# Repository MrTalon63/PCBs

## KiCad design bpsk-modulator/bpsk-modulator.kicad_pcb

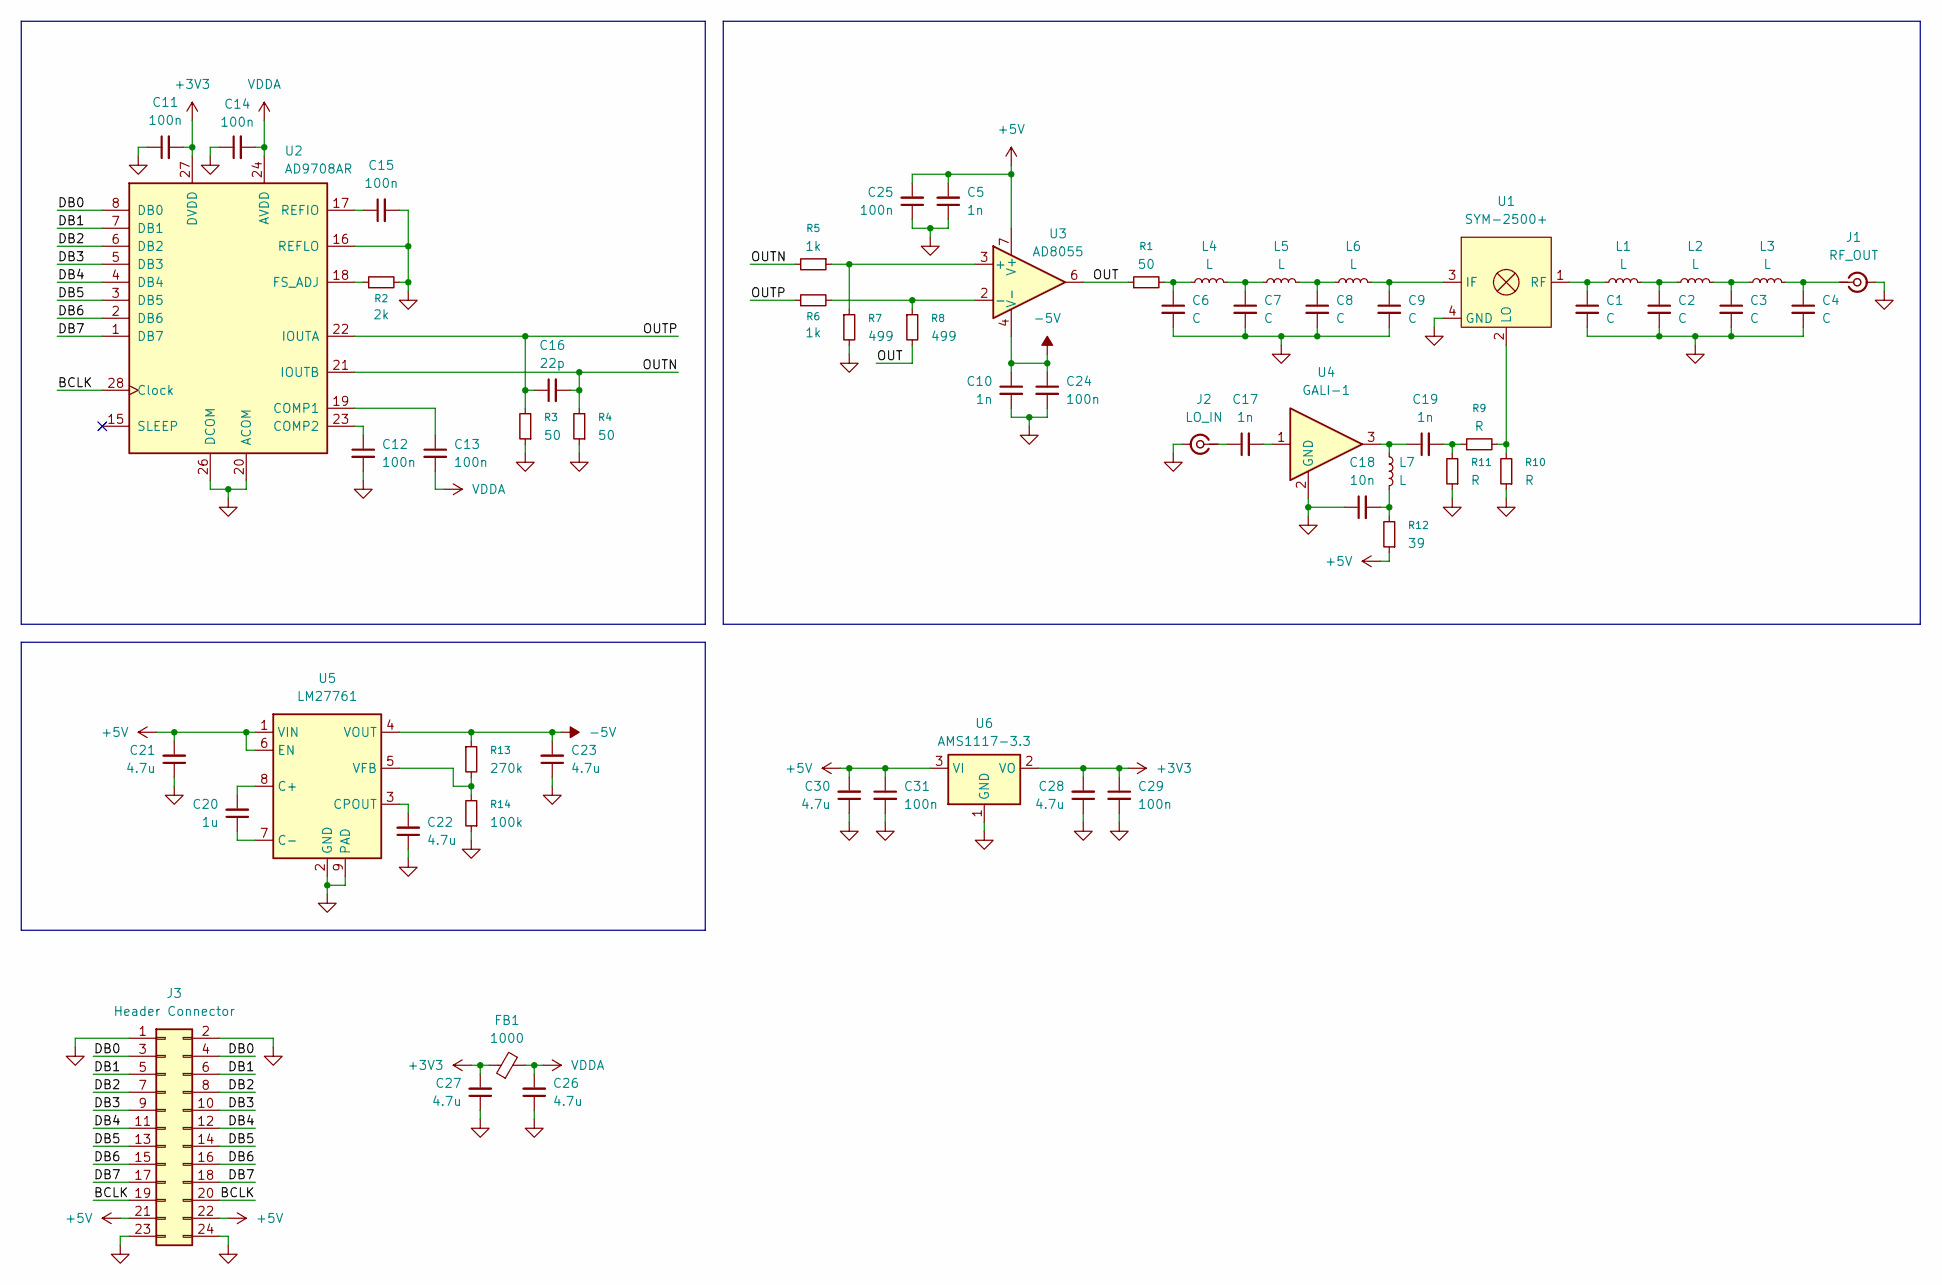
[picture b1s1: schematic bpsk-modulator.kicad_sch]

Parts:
C1, C2, C3, C4: C; C_0402_1005Metric
C5, C10, C17, C19: 1n; C_0603_1608Metric_Pad1.08x0.95mm_HandSolder
C6, C7, C8, C9: C; C_0603_1608Metric_Pad1.08x0.95mm_HandSolder
C11, C12, C13, C14, C15, C24, C25, C29, C31: 100n; C_0603_1608Metric_Pad1.08x0.95mm_HandSolder
C16: 22p; C_0603_1608Metric_Pad1.08x0.95mm_HandSolder
C18: 10n; C_0603_1608Metric_Pad1.08x0.95mm_HandSolder
C20: 1u; C_0603_1608Metric_Pad1.08x0.95mm_HandSolder
C21, C22, C23, C26, C27, C28, C30: 4.7u; C_0603_1608Metric_Pad1.08x0.95mm_HandSolder
FB1: 1000; L_0603_1608Metric
J1: RF_OUT; SMA_Samtec_SMA-J-P-H-ST-EM1_EdgeMount
J2: LO_IN; SMA_Samtec_SMA-J-P-H-ST-EM1_EdgeMount
J3: Header Connector; PinHeader_2x12_P2.54mm_Vertical
L1, L2, L3: L; L_0402_1005Metric
L4, L5, L6, L7: L; L_0603_1608Metric
R1, R3, R4: 50; R_0603_1608Metric_Pad0.98x0.95mm_HandSolder
R2: 2k; R_0603_1608Metric_Pad0.98x0.95mm_HandSolder
R5, R6: 1k; R_0603_1608Metric_Pad0.98x0.95mm_HandSolder
R7, R8: 499; R_0603_1608Metric_Pad0.98x0.95mm_HandSolder
R9, R10, R11: R; R_0603_1608Metric_Pad0.98x0.95mm_HandSolder
R12: 39; R_0603_1608Metric_Pad0.98x0.95mm_HandSolder
R13: 270k; R_0603_1608Metric_Pad0.98x0.95mm_HandSolder
R14: 100k; R_0603_1608Metric_Pad0.98x0.95mm_HandSolder
U1: SYM-2500+; Mini-Circuits_TTT167_LandPatternPL-079
U2: AD9708AR; TSSOP-28_4.4x9.7mm_P0.65mm
U3: AD8055; SOIC-8_3.9x4.9mm_P1.27mm
U4: GALI-1; SOT-89-3
U5: LM27761; WSON-8-1EP_2x2mm_P0.5mm_EP0.9x1.6mm
U6: AMS1117-3.3; SOT-223-3_TabPin2

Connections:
+3V3: C11.2, C27.2, C28.2, C29.1, FB1.1, U2.27 (DVDD), U6.2 (VO)
+5V: C5.2, C21.2, C25.2, C30.2, C31.1, J3.21, J3.22, R12.1, U3.7 (V+), U5.1 (VIN), U5.6 (EN), U6.3 (VI)
-5V: C10.1, C23.2, C24.1, R13.1, U3.4 (V-), U5.4 (VOUT)
/BCLK: J3.19, J3.20, U2.28 (Clock)
/DB0: J3.3, J3.4, U2.8 (DB0)
/DB1: J3.5, J3.6, U2.7 (DB1)
/DB2: J3.7, J3.8, U2.6 (DB2)
/DB3: J3.9, J3.10, U2.5 (DB3)
/DB4: J3.11, J3.12, U2.4 (DB4)
/DB5: J3.13, J3.14, U2.3 (DB5)
/DB6: J3.15, J3.16, U2.2 (DB6)
/DB7: J3.17, J3.18, U2.1 (DB7)
/OUT: R1.1, R8.2, U3.6
/OUTN: C16.2, R4.2, R5.2, U2.21 (IOUTB)
/OUTP: C16.1, R3.2, R6.1, U2.22 (IOUTA)
GND: C1.2, C2.2, C3.2, C4.2, C5.1, C6.2, C7.2, C8.2, C9.2, C10.2, C11.1, C12.2, C14.1, C15.2, C18.1, C21.1, C22.1, C23.1, C24.2, C25.1, C26.1, C27.1, C28.1, C29.2, C30.1, C31.2, J1.2 (Ext), J2.2 (Ext), J3.1, J3.2, J3.23, J3.24, R2.2, R3.1, R4.1, R7.2, R10.1, R11.1, R14.1, U1.4 (GND), U2.16 (REFLO), U2.20 (ACOM), U2.26 (DCOM), U4.2 (GND), U5.2 (GND), U5.9 (PAD), U6.1 (GND)
unnamed: C2.1, L1.2, L2.1
unnamed: C3.1, L2.2, L3.1
unnamed: C6.1, L4.1, R1.2
unnamed: C7.1, L4.2, L5.1
unnamed: C8.1, L5.2, L6.1
unnamed: C17.2, U4.1
unnamed: C18.2, L7.2, R12.2
unnamed: C19.1, L7.1, U4.3
unnamed: C19.2, R9.1, R11.2
unnamed: C4.1, J1.1 (In), L3.2
unnamed: C17.1, J2.1 (In)
unnamed: C9.1, L6.2, U1.3 (IF)
unnamed: R9.2, R10.2, U1.2 (LO)
unnamed: C1.1, L1.1, U1.1 (RF)
unnamed: C13.1, U2.19 (COMP1)
unnamed: C12.1, U2.23 (COMP2)
unnamed: R2.1, U2.18 (FS_ADJ)
unnamed: C15.1, U2.17 (REFIO)
unnamed: R5.1, R7.1, U3.3 (+)
unnamed: R6.2, R8.1, U3.2 (-)
unnamed: C20.2, U5.8 (C+)
unnamed: C20.1, U5.7 (C-)
unnamed: C22.2, U5.3 (CPOUT)
unnamed: R13.2, R14.2, U5.5 (VFB)
VDDA: C13.2, C14.2, C26.2, FB1.2, U2.24 (AVDD)

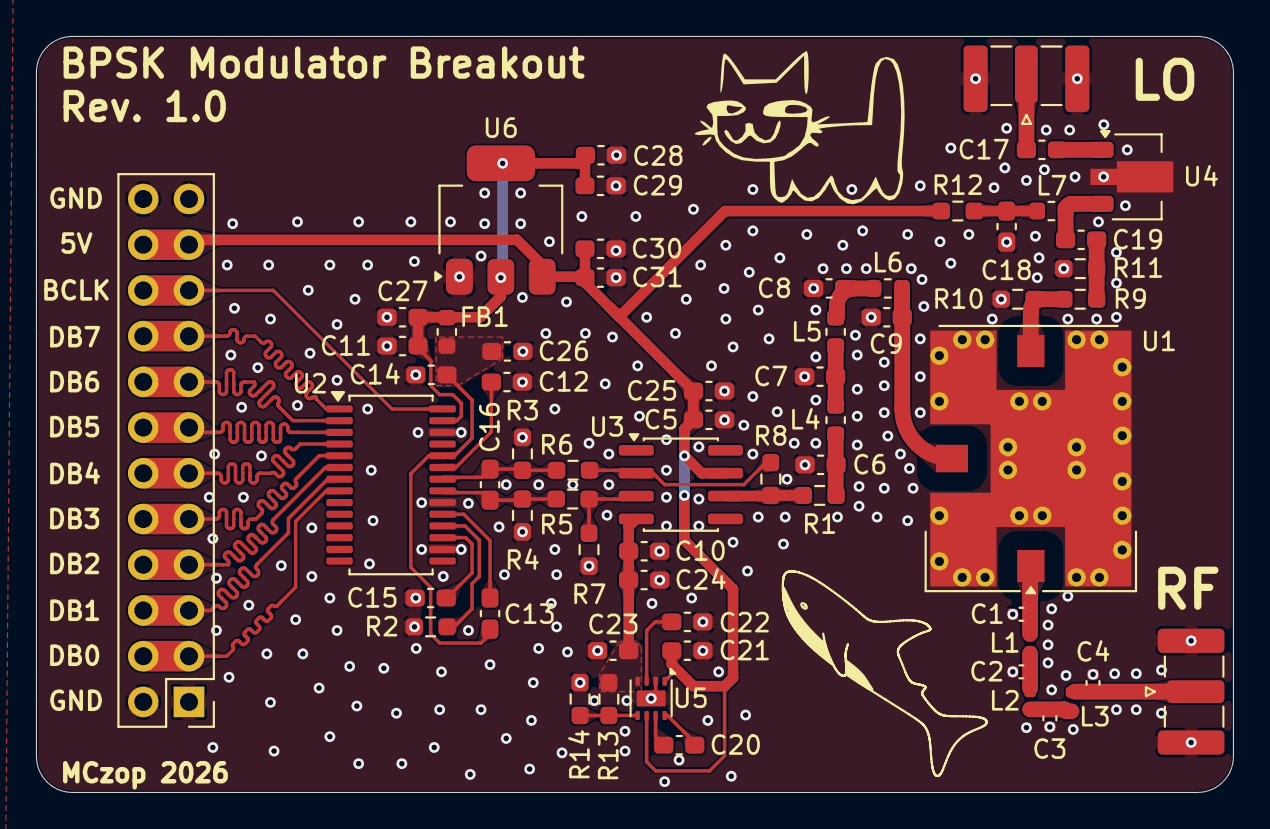
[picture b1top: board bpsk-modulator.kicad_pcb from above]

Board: 2 copper layers, 66.5 x 42.0 mm, 62 parts (0 on the bottom side), 41 nets.

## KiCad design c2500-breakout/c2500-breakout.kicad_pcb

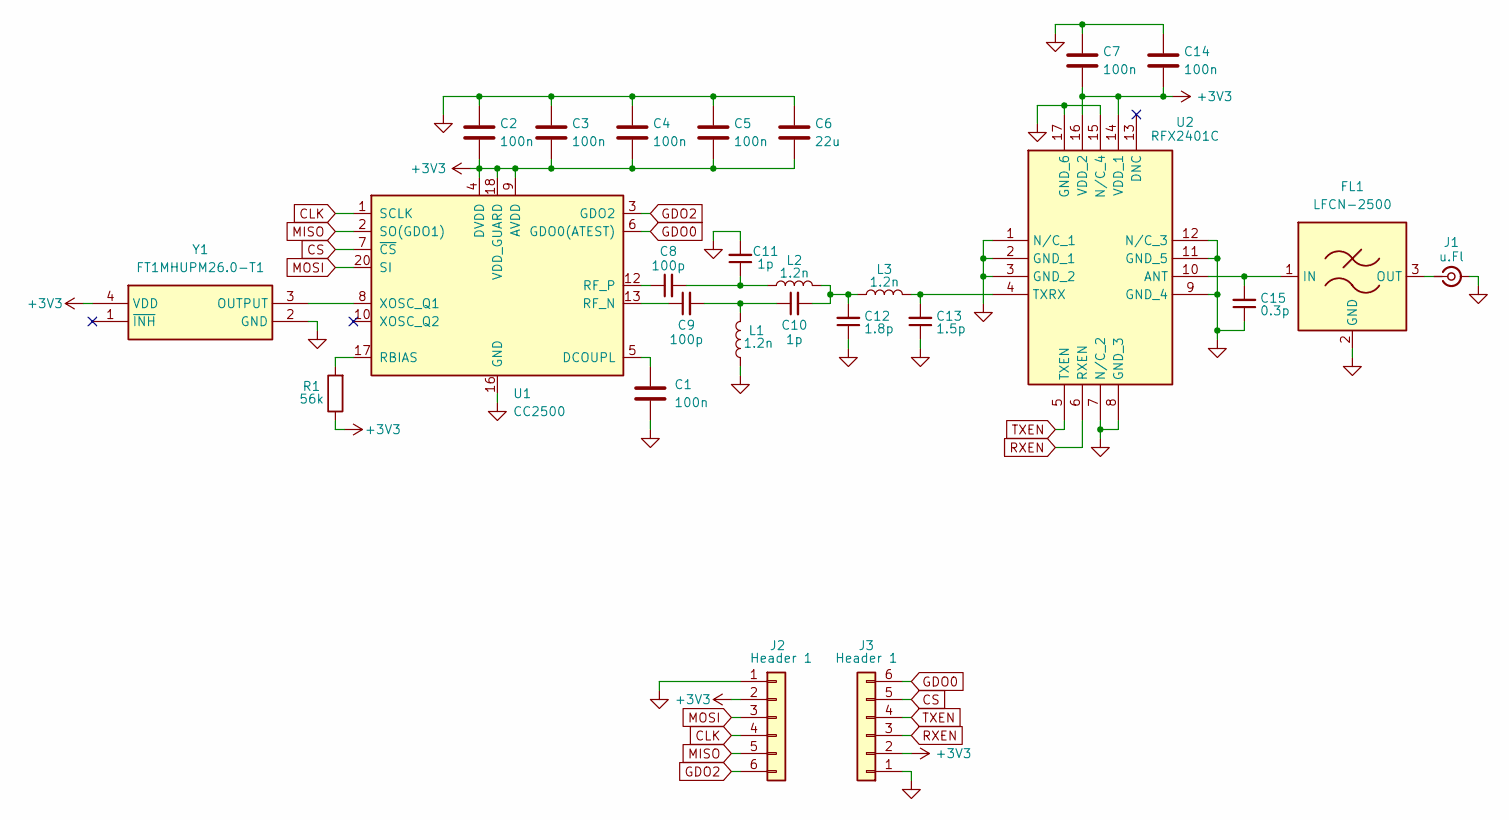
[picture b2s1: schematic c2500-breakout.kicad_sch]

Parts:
C1, C2, C3, C4, C5, C7, C14: 100n; C_0603_1608Metric_Pad1.08x0.95mm_HandSolder
C6: 22u; C_0603_1608Metric_Pad1.08x0.95mm_HandSolder
C8, C9: 100p; C_0402_1005Metric_Pad0.74x0.62mm_HandSolder
C10, C11: 1p; C_0402_1005Metric_Pad0.74x0.62mm_HandSolder
C12: 1.8p; C_0402_1005Metric_Pad0.74x0.62mm_HandSolder
C13: 1.5p; C_0402_1005Metric_Pad0.74x0.62mm_HandSolder
C15: 0.3p; C_0402_1005Metric_Pad0.74x0.62mm_HandSolder
FL1: LFCN-2500; Filter_Mini-Circuits_FV1206
J1: u.Fl; U.FL_Molex_MCRF_73412-0110_Vertical
J2, J3: Header 1; PinHeader_1x06_P2.54mm_Vertical
L1, L2, L3: 1.2n; L_0402_1005Metric_Pad0.77x0.64mm_HandSolder
R1: 56k; R_0603_1608Metric_Pad0.98x0.95mm_HandSolder
U1: CC2500; Texas_RGP0020H_VQFN-20-1EP_4x4mm_P0.5mm_EP2.4x2.4mm
U2: RFX2401C; QFN50P300X300X60-17N-D; Mouser Part Number 477-RFX2401C
Y1: FT1MHUPM26.0-T1; FT1MHUPM260T1; Manufacturer_Part_Number FT1MHUPM26.0-T1

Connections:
+3V3: C2.2, C3.2, C4.2, C5.2, C6.2, C7.2, C14.2, J2.2, J3.2, R1.1, U1.4 (DVDD), U1.9 (AVDD), U1.11 (AVDD), U1.14 (AVDD), U1.15 (AVDD), U1.18 (VDD_GUARD), U2.14 (VDD_1), U2.16 (VDD_2), Y1.4 (VDD)
CLK: J2.4, U1.1 (SCLK)
CS: J3.5, U1.7 (~CS)
GDO0: J3.6, U1.6 (GDO0(ATEST))
GDO2: J2.6, U1.3 (GDO2)
GND: C1.2, C2.1, C3.1, C4.1, C5.1, C6.1, C7.1, C11.2, C12.1, C13.1, C14.1, C15.1, FL1.2 (GND), FL1.4 (GND), J1.2 (Ext), J2.1, J3.1, L1.1, U1.16 (GND), U1.19 (GND), U1.21 (GND), U2.1 (N/C_1), U2.2 (GND_1), U2.3 (GND_2), U2.7 (N/C_2), U2.8 (GND_3), U2.9 (GND_4), U2.11 (GND_5), U2.12 (N/C_3), U2.15 (N/C_4), U2.17 (GND_6), Y1.2 (GND)
MISO: J2.5, U1.2 (SO(GDO1))
MOSI: J2.3, U1.20 (SI)
unnamed: C9.2, C10.1, L1.2
unnamed: C10.2, C12.2, L2.2, L3.1
unnamed: C8.2, C11.1, L2.1
unnamed: C15.2, FL1.1 (IN), U2.10 (ANT)
unnamed: FL1.3 (OUT), J1.1 (In)
unnamed: C1.1, U1.5 (DCOUPL)
unnamed: R1.2, U1.17 (RBIAS)
unnamed: C9.1, U1.13 (RF_N)
unnamed: C8.1, U1.12 (RF_P)
unnamed: U1.8 (XOSC_Q1), Y1.3 (OUTPUT)
unnamed: C13.2, L3.2, U2.4 (TXRX)
RXEN: J3.3, U2.6 (RXEN)
TXEN: J3.4, U2.5 (TXEN)

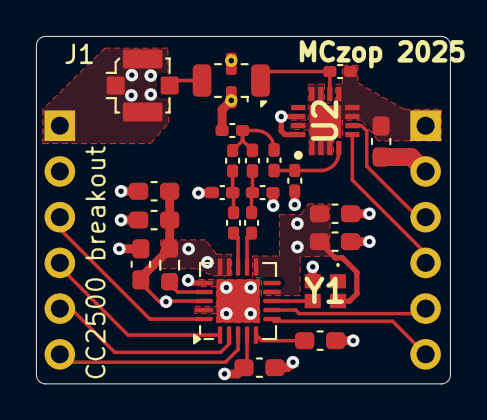
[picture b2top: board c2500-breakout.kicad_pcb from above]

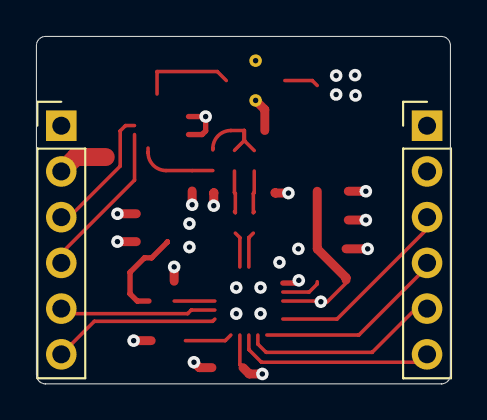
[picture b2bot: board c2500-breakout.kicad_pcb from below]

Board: 6 copper layers, 23.0 x 19.3 mm, 26 parts (2 on the bottom side), 21 nets.

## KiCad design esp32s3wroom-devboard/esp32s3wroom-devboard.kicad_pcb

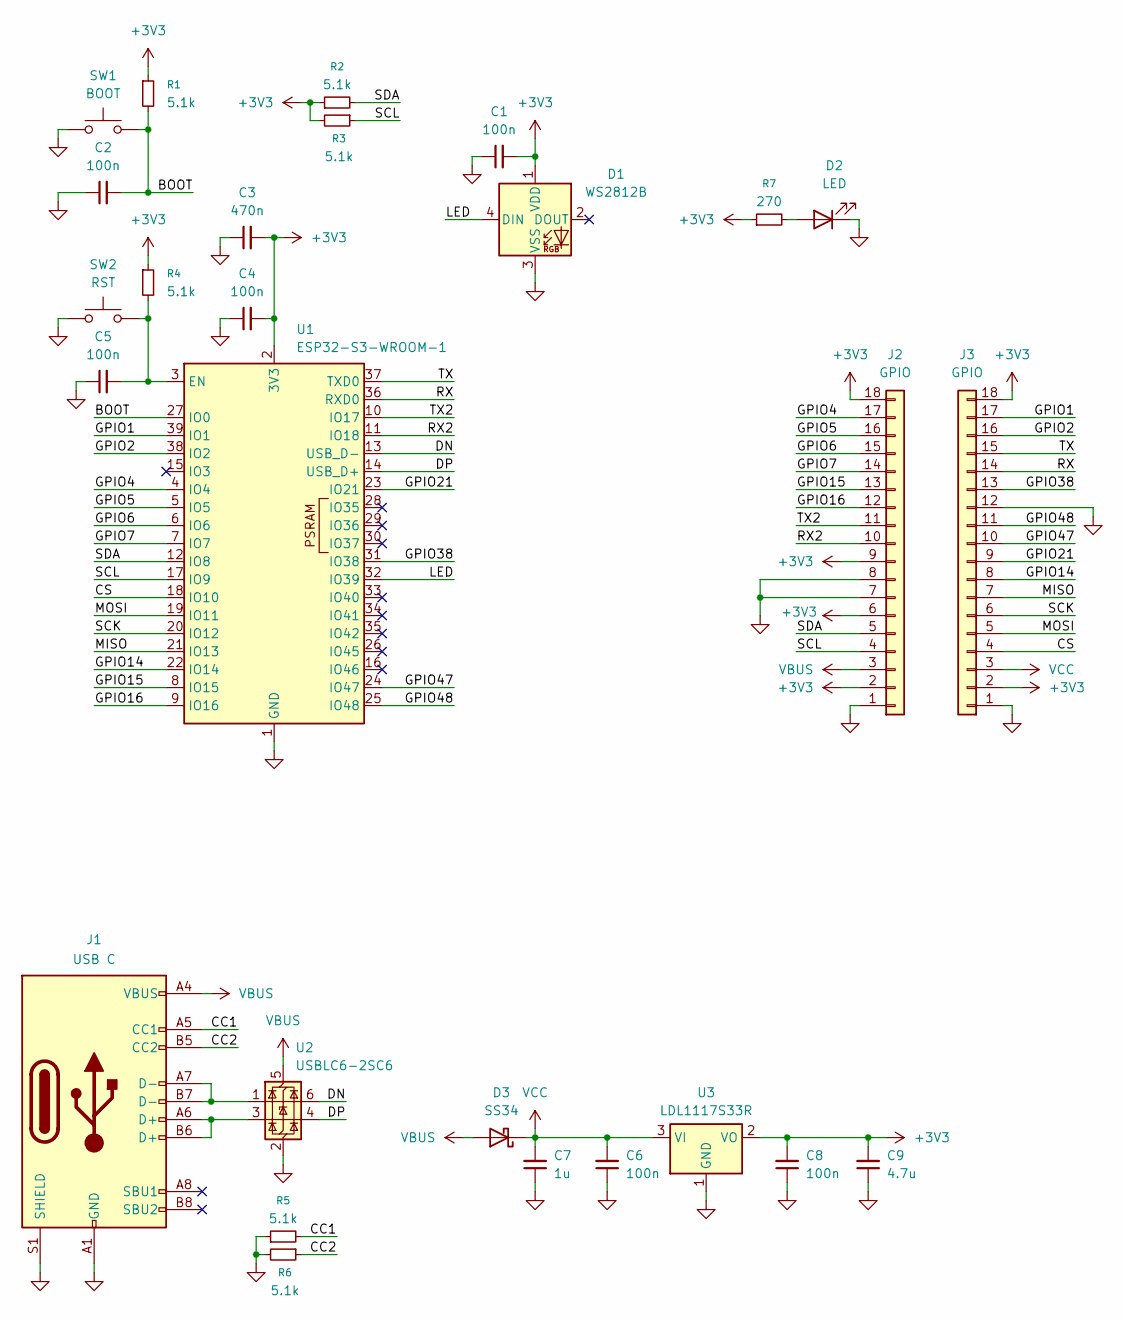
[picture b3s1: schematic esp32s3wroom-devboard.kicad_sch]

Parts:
C1, C2, C4, C5, C6, C8: 100n; C_0402_1005Metric
C3: 470n; C_0402_1005Metric
C7: 1u; C_0603_1608Metric
C9: 4.7u; C_0603_1608Metric
D1: WS2812B; LED_WS2812B_PLCC4_5.0x5.0mm_P3.2mm
D2: LED; LED_0805_2012Metric
D3: SS34; D_SMA
J1: USB C; USB_C_Receptacle_GCT_USB4105-xx-A_16P_TopMnt_Horizontal
J2, J3: GPIO; PinHeader_1x18_P2.54mm_Vertical
R1, R2, R3, R4, R5, R6: 5.1k; R_0402_1005Metric
R7: 270; R_0603_1608Metric
SW1: BOOT; KLS7TS6611
SW2: RST; KLS7TS6611
U1: ESP32-S3-WROOM-1
U2: USBLC6-2SC6; SOT-23-6
U3: LDL1117S33R; SOT-223-3_TabPin2

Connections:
+3V3: C1.2, C3.2, C4.2, C8.2, C9.2, D1.1 (VDD), J2.2, J2.6, J2.9, J2.18, J3.2, J3.18, R1.1, R2.1, R3.2, R4.1, R7.1, U1.2 (3V3), U3.2 (VO)
/BOOT: C2.2, R1.2, SW1.2, U1.27 (IO0)
/CC1: J1.A5 (CC1), R5.2
/CC2: J1.B5 (CC2), R6.1
/CS: J3.4, U1.18 (IO10)
/DN: U1.13 (USB_D-), U2.6 (I/O1)
/DP: U1.14 (USB_D+), U2.4 (I/O2)
/GPIO1: J3.17, U1.39 (IO1)
/GPIO2: J3.16, U1.38 (IO2)
/GPIO4: J2.17, U1.4 (IO4)
/GPIO5: J2.16, U1.5 (IO5)
/GPIO6: J2.15, U1.6 (IO6)
/GPIO7: J2.14, U1.7 (IO7)
/GPIO14: J3.8, U1.22 (IO14)
/GPIO15: J2.13, U1.8 (IO15)
/GPIO16: J2.12, U1.9 (IO16)
/GPIO21: J3.9, U1.23 (IO21)
/GPIO38: J3.13, U1.31 (IO38)
/GPIO47: J3.10, U1.24 (IO47)
/GPIO48: J3.11, U1.25 (IO48)
/LED: D1.4 (DIN), U1.32 (IO39)
/MISO: J3.7, U1.21 (IO13)
/MOSI: J3.5, U1.19 (IO11)
/RX: J3.14, U1.36 (RXD0)
/RX2: J2.10, U1.11 (IO18)
/SCK: J3.6, U1.20 (IO12)
/SCL: J2.4, R3.1, U1.17 (IO9)
/SDA: J2.5, R2.2, U1.12 (IO8)
/TX: J3.15, U1.37 (TXD0)
/TX2: J2.11, U1.10 (IO17)
GND: C1.1, C2.1, C3.1, C4.1, C5.1, C6.1, C7.1, C8.1, C9.1, D1.3 (VSS), D2.1 (K), J1.A1 (GND), J1.A12 (GND), J1.B1 (GND), J1.B12 (GND), J1.S1 (SHIELD), J2.1, J2.7, J2.8, J3.1, J3.12, R5.1, R6.2, SW1.1, SW2.1, U1.1 (GND), U1.40 (GND), U1.41 (GND), U2.2 (GND), U3.1 (GND)
unnamed: D2.2 (A), R7.2
unnamed: J1.A6 (D+), J1.B6 (D+), U2.3 (I/O2)
unnamed: J1.A7 (D-), J1.B7 (D-), U2.1 (I/O1)
unnamed: C5.2, R4.2, SW2.2, U1.3 (EN)
VBUS: D3.2 (A), J1.A4 (VBUS), J1.A9 (VBUS), J1.B4 (VBUS), J1.B9 (VBUS), J2.3, U2.5 (VBUS)
VCC: C6.2, C7.2, D3.1 (K), J3.3, U3.3 (VI)

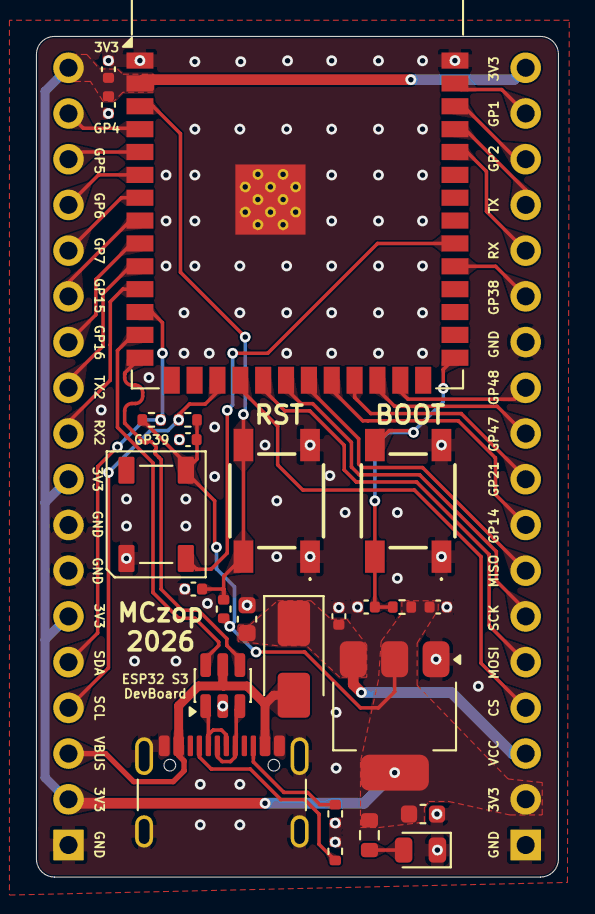
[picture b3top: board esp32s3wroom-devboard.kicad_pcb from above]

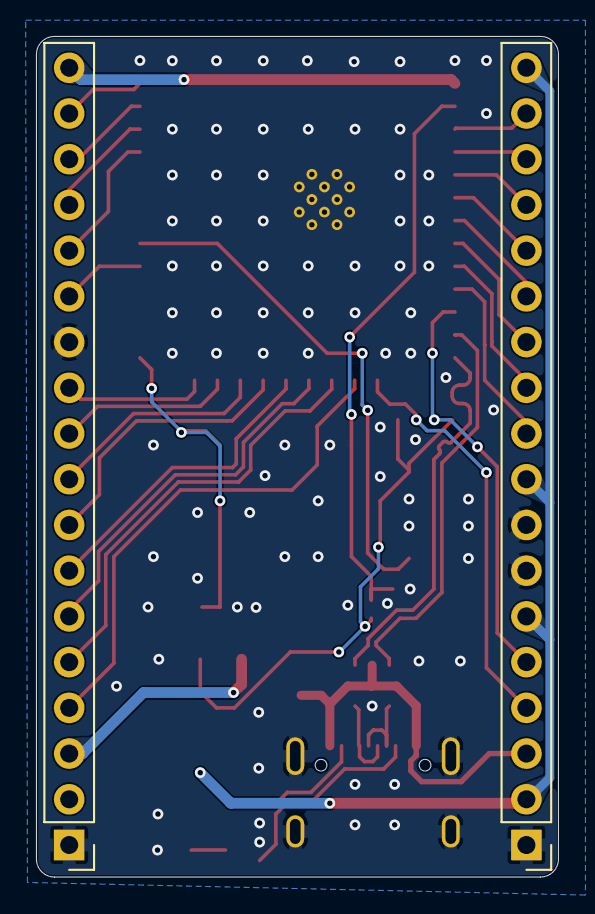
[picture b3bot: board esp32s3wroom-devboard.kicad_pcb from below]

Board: 2 copper layers, 29.0 x 46.7 mm, 27 parts (2 on the bottom side), 37 nets.

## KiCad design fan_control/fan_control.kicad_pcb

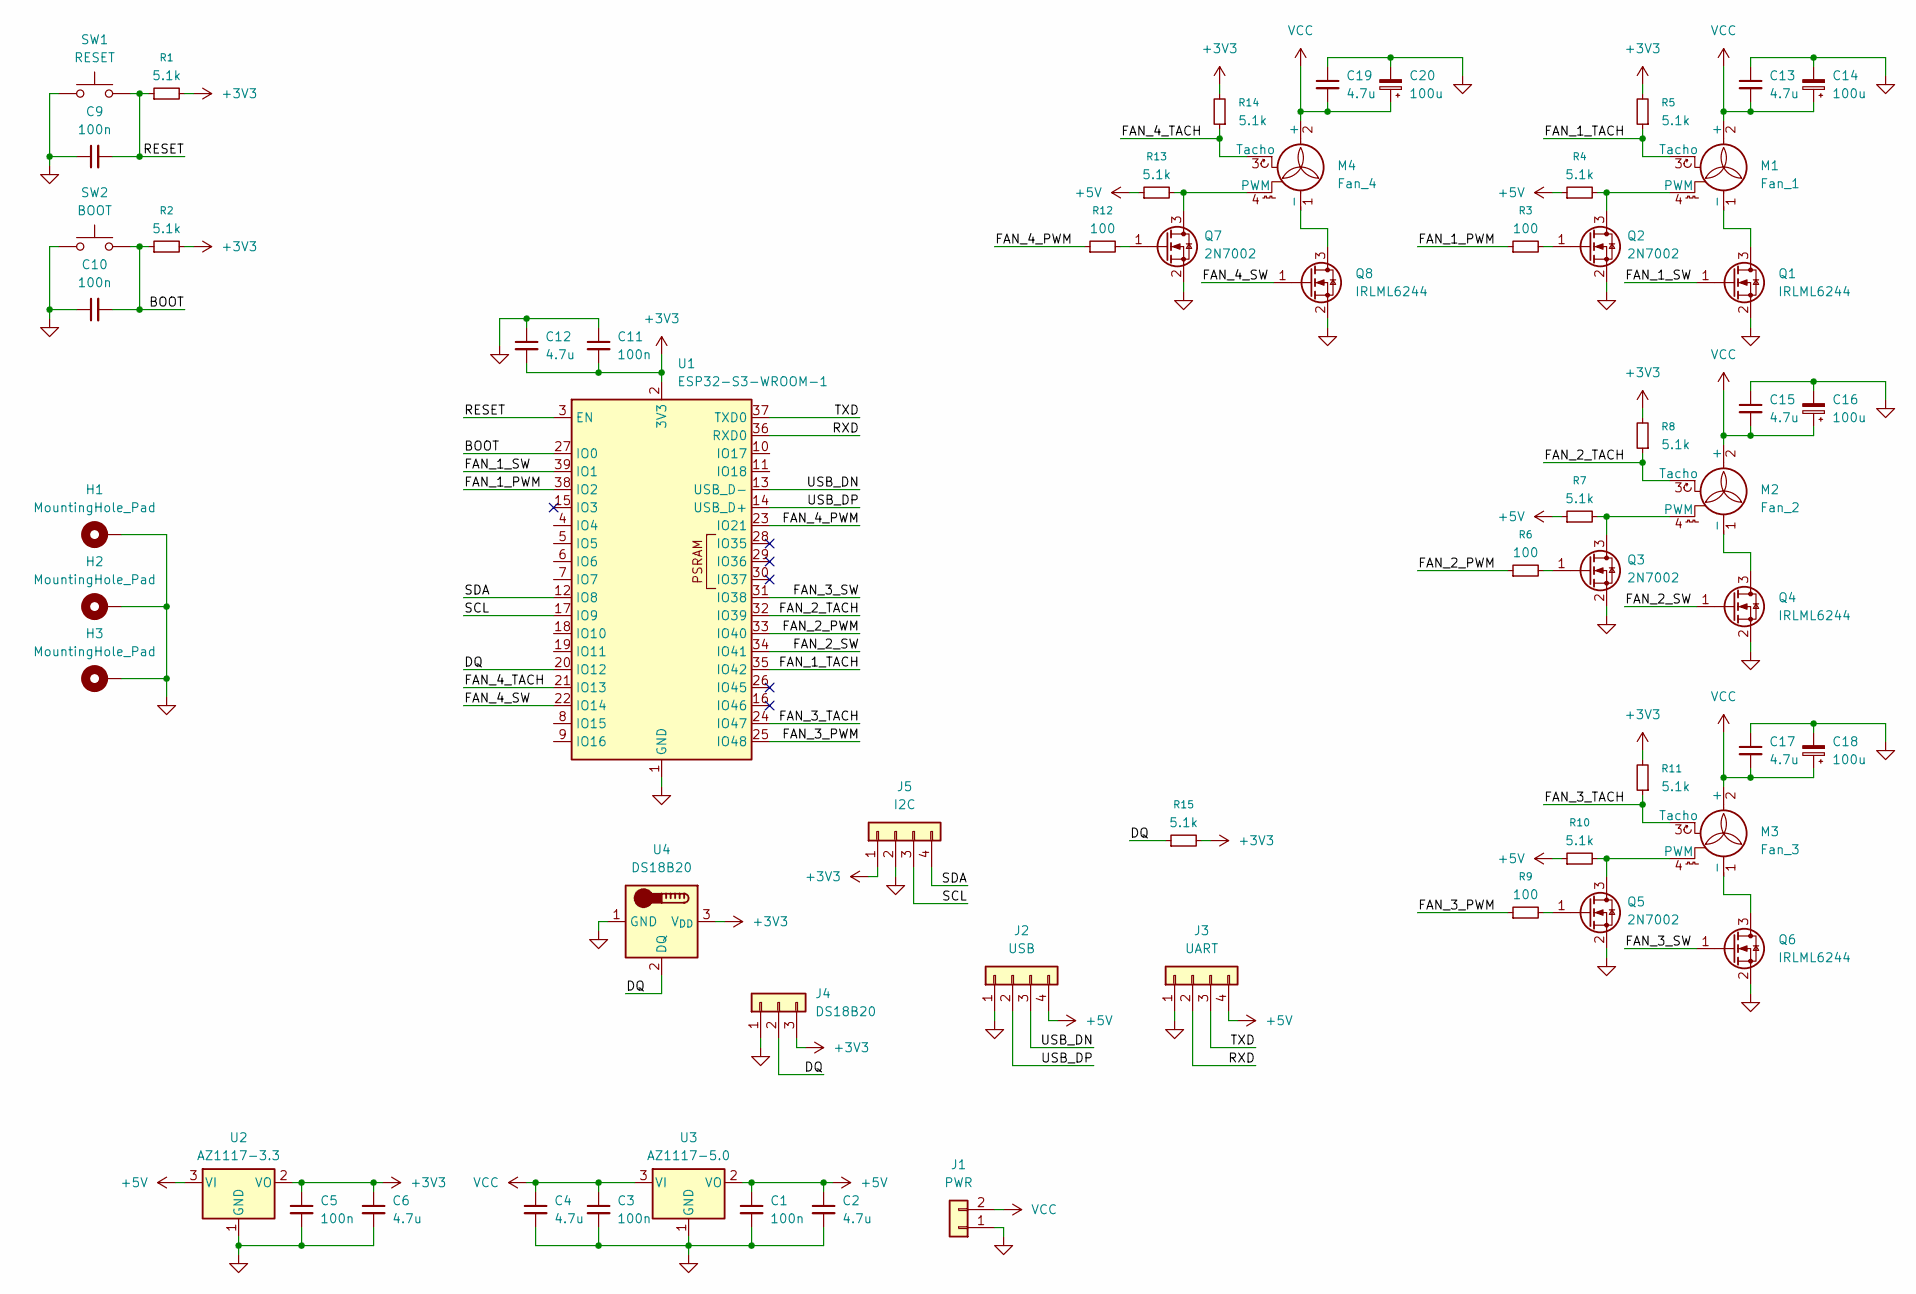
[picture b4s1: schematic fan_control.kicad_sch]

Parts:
C1, C3, C5, C9, C10, C11: 100n; C_0603_1608Metric_Pad1.08x0.95mm_HandSolder
C2, C4, C6, C12, C13, C15, C17, C19: 4.7u; C_0603_1608Metric_Pad1.08x0.95mm_HandSolder
C14, C16, C18, C20: 100u; CP_Radial_D5.0mm_P2.00mm
H1, H2, H3: MountingHole_Pad; MountingHole_2.7mm_M2.5_DIN965_Pad_TopBottom
J1: PWR; SolderWire-0.5sqmm_1x02_P4.6mm_D0.9mm_OD2.1mm
J2: USB; PinHeader_1x04_P2.54mm_Vertical
J3: UART; PinHeader_1x04_P2.54mm_Vertical
J4: DS18B20; PinSocket_1x03_P2.54mm_Vertical
J5: I2C; PinHeader_1x04_P2.54mm_Vertical
M1: Fan_1; FanPinHeader_1x04_P2.54mm_Vertical
M2: Fan_2; FanPinHeader_1x04_P2.54mm_Vertical
M3: Fan_3; FanPinHeader_1x04_P2.54mm_Vertical
M4: Fan_4; FanPinHeader_1x04_P2.54mm_Vertical
Q1, Q4, Q6, Q8: IRLML6244; SOT-23-3
Q2, Q3, Q5, Q7: 2N7002; SOT-23-3
R1, R2: 5.1k; R_0603_1608Metric_Pad0.98x0.95mm_HandSolder
R3, R6, R9, R12: 100; R_0603_1608Metric
R4, R5, R7, R8, R10, R11, R13, R14, R15: 5.1k; R_0603_1608Metric
SW1: RESET; SW_SPST_PTS645Sx43SMTR92
SW2: BOOT; SW_SPST_PTS645Sx43SMTR92
U1: ESP32-S3-WROOM-1
U2: AZ1117-3.3; SOT-223-3_TabPin2
U3: AZ1117-5.0; SOT-223-3_TabPin2
U4: DS18B20; TO-92_HandSolder

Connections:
+3V3: C5.1, C6.1, C11.2, C12.2, J4.3, J5.1, R1.2, R2.2, R5.2, R8.2, R11.2, R14.2, R15.2, U1.2 (3V3), U2.2 (VO), U4.3 (V_{DD})
+5V: C1.1, C2.1, J2.4, J3.4, R4.1, R7.1, R10.1, R13.1, U2.3 (VI), U3.2 (VO)
/BOOT: C10.2, R2.1, SW2.2, U1.27 (IO0)
/DQ: J4.2, R15.1, U1.20 (IO12), U4.2 (DQ)
/FAN_1_PWM: R3.1, U1.38 (IO2)
/FAN_1_SW: Q1.1 (G), U1.39 (IO1)
/FAN_1_TACH: M1.3 (Tacho), R5.1, U1.35 (IO42)
/FAN_2_PWM: R6.1, U1.33 (IO40)
/FAN_2_SW: Q4.1 (G), U1.34 (IO41)
/FAN_2_TACH: M2.3 (Tacho), R8.1, U1.32 (IO39)
/FAN_3_PWM: R9.1, U1.25 (IO48)
/FAN_3_SW: Q6.1 (G), U1.31 (IO38)
/FAN_3_TACH: M3.3 (Tacho), R11.1, U1.24 (IO47)
/FAN_4_PWM: R12.1, U1.23 (IO21)
/FAN_4_SW: Q8.1 (G), U1.22 (IO14)
/FAN_4_TACH: M4.3 (Tacho), R14.1, U1.21 (IO13)
/RESET: C9.2, R1.1, SW1.2, U1.3 (EN)
/RXD: J3.2, U1.36 (RXD0)
/SCL: J5.3, U1.17 (IO9)
/SDA: J5.4, U1.12 (IO8)
/TXD: J3.3, U1.37 (TXD0)
/USB_DN: J2.3, U1.13 (USB_D-)
/USB_DP: J2.2, U1.14 (USB_D+)
GND: C1.2, C2.2, C3.2, C4.2, C5.2, C6.2, C9.1, C10.1, C11.1, C12.1, C13.1, C14.2, C15.1, C16.2, C17.1, C18.2, C19.1, C20.2, H1.1, H2.1, H3.1, J1.1, J2.1, J3.1, J4.1, J5.2, Q1.2 (S), Q2.2 (S), Q3.2 (S), Q4.2 (S), Q5.2 (S), Q6.2 (S), Q7.2 (S), Q8.2 (S), SW1.1, SW2.1, U1.1 (GND), U1.40 (GND), U1.41 (GND), U2.1 (GND), U3.1 (GND), U4.1 (GND)
unnamed: M1.1 (-), Q1.3 (D)
unnamed: M1.4 (PWM), Q2.3 (D), R4.2
unnamed: M2.1 (-), Q4.3 (D)
unnamed: M2.4 (PWM), Q3.3 (D), R7.2
unnamed: M3.1 (-), Q6.3 (D)
unnamed: M3.4 (PWM), Q5.3 (D), R10.2
unnamed: M4.1 (-), Q8.3 (D)
unnamed: M4.4 (PWM), Q7.3 (D), R13.2
unnamed: Q2.1 (G), R3.2
unnamed: Q3.1 (G), R6.2
unnamed: Q5.1 (G), R9.2
unnamed: Q7.1 (G), R12.2
VCC: C3.1, C4.1, C13.2, C14.1, C15.2, C16.1, C17.2, C18.1, C19.2, C20.1, J1.2, M1.2 (+), M2.2 (+), M3.2 (+), M4.2 (+), U3.3 (VI)

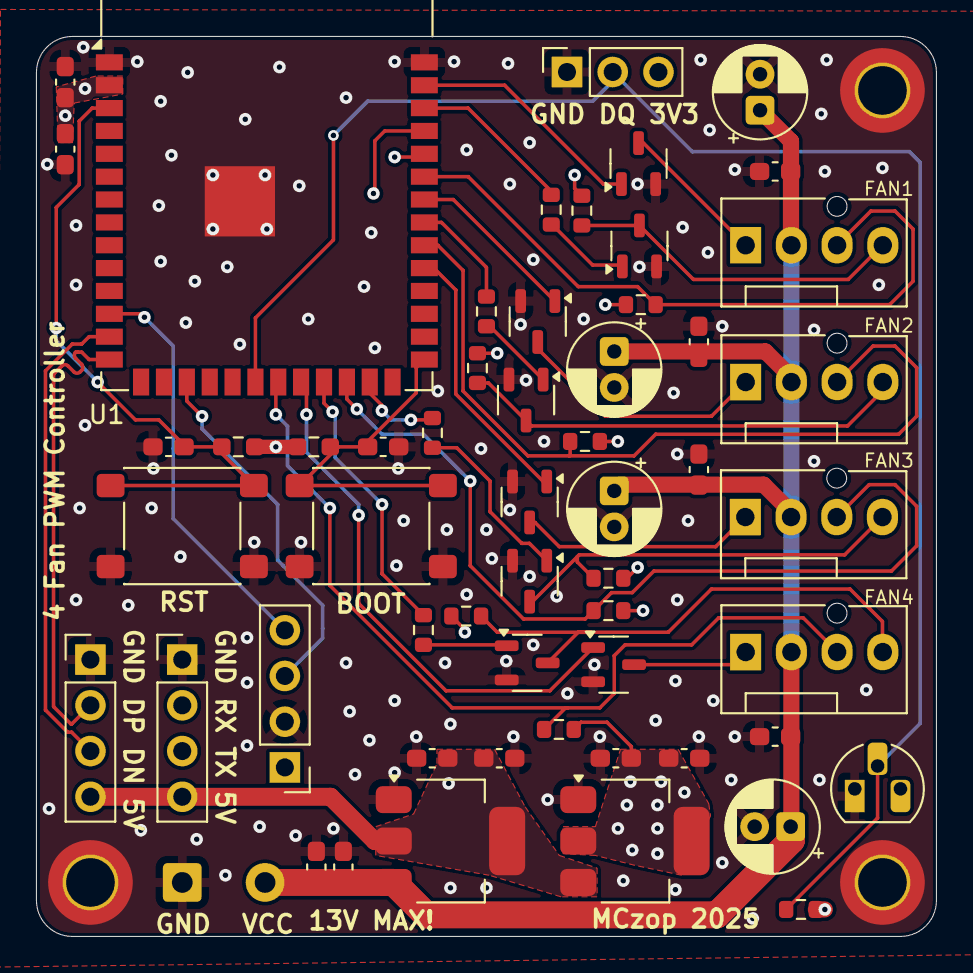
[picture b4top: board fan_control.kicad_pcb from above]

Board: 6 copper layers, 50.0 x 50.0 mm, 59 parts (0 on the bottom side), 37 nets.

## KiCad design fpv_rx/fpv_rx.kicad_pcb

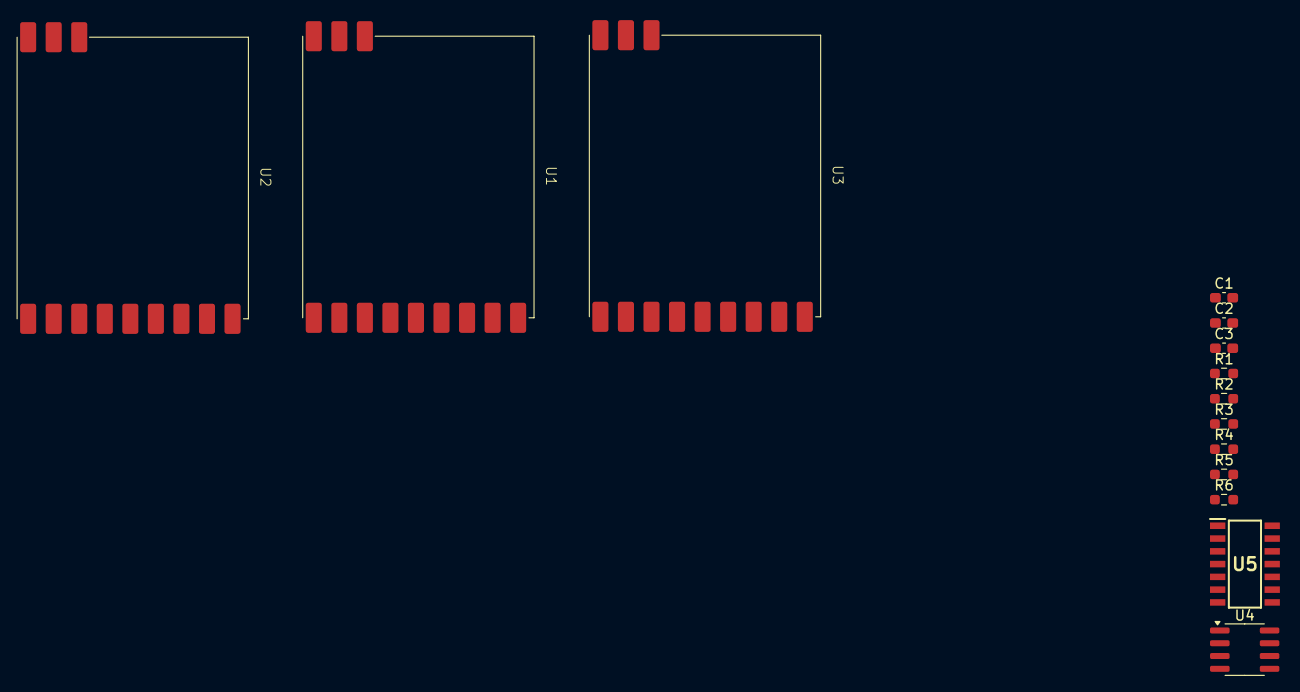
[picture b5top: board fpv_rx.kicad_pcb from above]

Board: 2 copper layers, 14 parts (0 on the bottom side), 8 nets, no tracks yet.

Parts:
C1, C2, C3: 100n; C_0603_1608Metric_Pad1.08x0.95mm_HandSolder
R1, R2, R3, R4, R5: 75; R_0603_1608Metric_Pad0.98x0.95mm_HandSolder
R6: 680k; R_0603_1608Metric_Pad0.98x0.95mm_HandSolder
U1, U2, U3: RX5808
U4: LM1881; SOIC-8_3.9x4.9mm_P1.27mm
U5: MAX4314ESD+; SOIC127P600X175-14N

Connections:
+5V: C1.1, C2.2, U1.8 (VCC), U2.8 (VCC), U3.8 (VCC), U4.8 (VCC), U5.4 (VCC), U5.12 (~SHDN)
/VIDEO_1: R2.1, U1.5 (VIDEO), U5.5 (IN0)
/VIDEO_2: R1.1, U2.5 (VIDEO), U5.7 (IN1)
/VIDEO_3: R4.1, U3.5 (VIDEO), U5.8 (IN2)
/VIDEO_4: R3.1, U5.10 (IN3)
GND: C1.2, C2.1, C3.2, R1.2, R2.2, R3.2, R4.2, R6.2, U1.1 (GND), U1.3 (GND), U1.4 (GND), U1.9 (GND), U2.1 (GND), U2.3 (GND), U2.4 (GND), U2.9 (GND), U3.1 (GND), U3.3 (GND), U3.4 (GND), U3.9 (GND), U4.4 (GND), U5.11 (VEE), U5.13 (GND)
unnamed: C3.1, R6.1, U4.6 (RSET)
unnamed: R5.1, U5.14 (OUT)

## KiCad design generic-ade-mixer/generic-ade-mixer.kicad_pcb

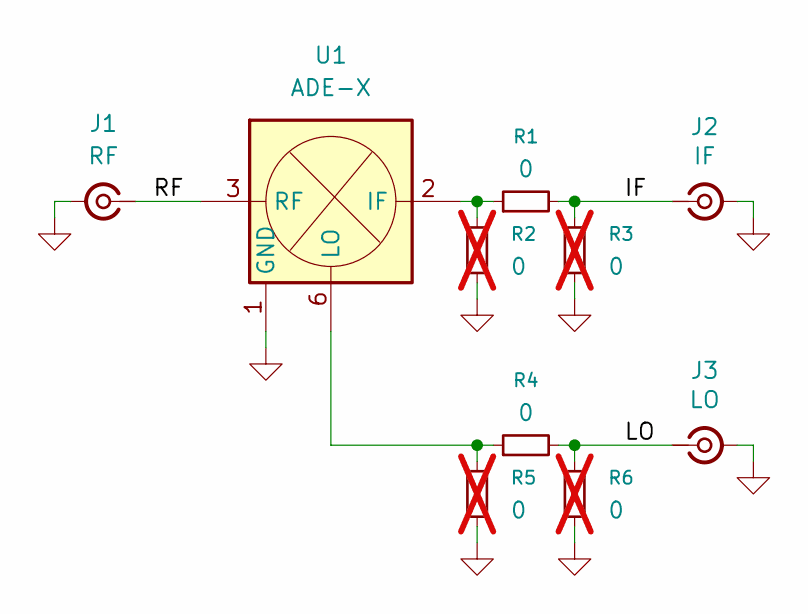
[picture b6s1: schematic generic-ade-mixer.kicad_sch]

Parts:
J1: RF; SMA_Samtec_SMA-J-P-H-ST-EM1_EdgeMount
J2: IF; SMA_Samtec_SMA-J-P-H-ST-EM1_EdgeMount
J3: LO; SMA_Samtec_SMA-J-P-H-ST-EM1_EdgeMount
R1, R4: 0; R_0603_1608Metric_Pad0.98x0.95mm_HandSolder
R2, R3, R5, R6: 0; R_0603_1608Metric_Pad0.98x0.95mm_HandSolder; not fitted
U1: ADE-X; Mini-Circuits_CD542_LandPatternPL-052

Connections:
/IF: J2.1 (In), R1.2, R3.2
/LO: J3.1 (In), R4.2, R6.2
/RF: J1.1 (In), U1.3 (RF)
GND: J1.2 (Ext), J2.2 (Ext), J3.2 (Ext), R2.1, R3.1, R5.1, R6.1, U1.1 (GND), U1.4 (GND), U1.5 (GND)
unnamed: R1.1, R2.2, U1.2 (IF)
unnamed: R4.1, R5.2, U1.6 (LO)

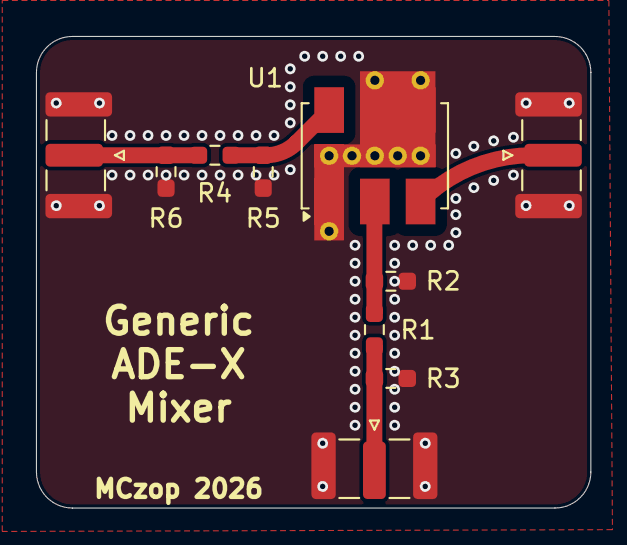
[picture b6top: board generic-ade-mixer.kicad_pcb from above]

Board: 2 copper layers, 30.8 x 26.2 mm, 10 parts (0 on the bottom side), 6 nets.

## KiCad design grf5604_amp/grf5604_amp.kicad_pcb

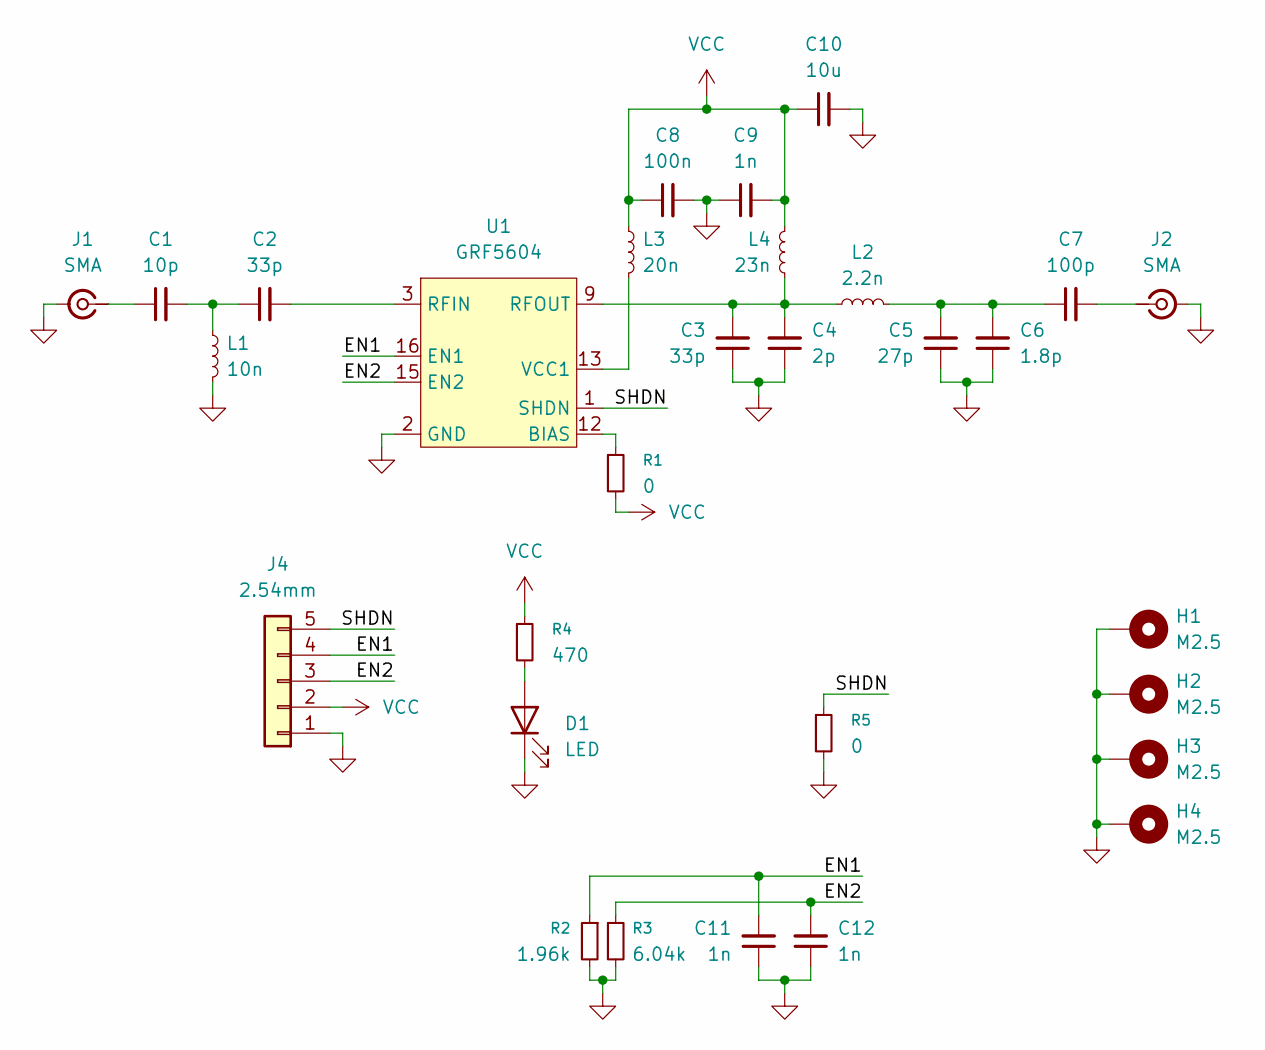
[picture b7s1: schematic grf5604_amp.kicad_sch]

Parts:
C1: 10p; C_0603_1608Metric
C2, C3: 33p; C_0603_1608Metric
C4: 2p; C_0603_1608Metric
C5: 27p; C_0603_1608Metric
C6: 1.8p; C_0603_1608Metric
C7: 100p; C_0603_1608Metric
C8: 100n; C_0603_1608Metric
C9, C11, C12: 1n; C_0603_1608Metric
C10: 10u; C_0805_2012Metric
D1: LED; LED_0805_2012Metric_Pad1.15x1.40mm_HandSolder
H1, H2, H3, H4: M2.5; MountingHole_2.7mm_M2.5_DIN965_Pad_TopBottom
J1, J2: SMA; SMA_Samtec_SMA-J-P-H-ST-EM1_EdgeMount
J4: 2.54mm; PinHeader_1x05_P2.54mm_Vertical
L1: 10n; L_0603_1608Metric
L2: 2.2n; L_0603_1608Metric
L3: 20n; L_0603_1608Metric
L4: 23n; L_0603_1608Metric
R1, R5: 0; R_0603_1608Metric_Pad0.98x0.95mm_HandSolder
R2: 1.96k; R_0603_1608Metric_Pad0.98x0.95mm_HandSolder
R3: 6.04k; R_0603_1608Metric_Pad0.98x0.95mm_HandSolder
R4: 470; R_0603_1608Metric
U1: GRF5604; QFN-16-1EP_3x3mm_P0.5mm_EP1.7x1.7mm

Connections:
/EN1: C11.2, J4.4, R2.1, U1.16 (EN1)
/EN2: C12.2, J4.3, R3.1, U1.15 (EN2)
/SHDN: J4.5, R5.1, U1.1 (SHDN)
GND: C3.1, C4.1, C5.1, C6.1, C8.2, C9.1, C10.2, C11.1, C12.1, D1.1 (K), H1.1 (1_1), H2.1 (1_1), H3.1 (1_1), H4.1 (1_1), J1.2 (Ext), J2.2 (Ext), J4.1, L1.2, R2.2, R3.2, R5.2, U1.2 (GND), U1.5 (GND), U1.6 (GND), U1.7 (GND), U1.8 (GND), U1.11 (GND), U1.14 (GND), U1.17 (GND)
unnamed: C1.2, C2.1, L1.1
unnamed: C2.2, U1.3 (RFIN), U1.4 (RFIN)
unnamed: C3.2, C4.2, L2.1, L4.2, U1.9 (RFOUT), U1.10 (RFOUT)
unnamed: C5.2, C6.2, C7.1, L2.2
unnamed: D1.2 (A), R4.2
unnamed: C1.1, J1.1 (In)
unnamed: C7.2, J2.1 (In)
unnamed: R1.1, U1.12 (BIAS)
unnamed: L3.2, U1.13 (VCC1)
VCC: C8.1, C9.2, C10.1, J4.2, L3.1, L4.1, R1.2, R4.1
